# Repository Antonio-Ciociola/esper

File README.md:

# Esper

An esp32 based eurorack module.

## Specifications

- 8HP width
- 4 CV inputs
- 2 Audio Outputs
- Oled Display with LVGL GUI
- Rotary Encoder with Push Button
- Esp32s3 has 2 cores, Bluetooth and Wifi support

## Photos

## Future Plans and Issues

- Better alternative to external adc for cv inputs
- Codec chip for both audio in and out, to allow for audio processing
- The esp32s3 floating point performance is not great

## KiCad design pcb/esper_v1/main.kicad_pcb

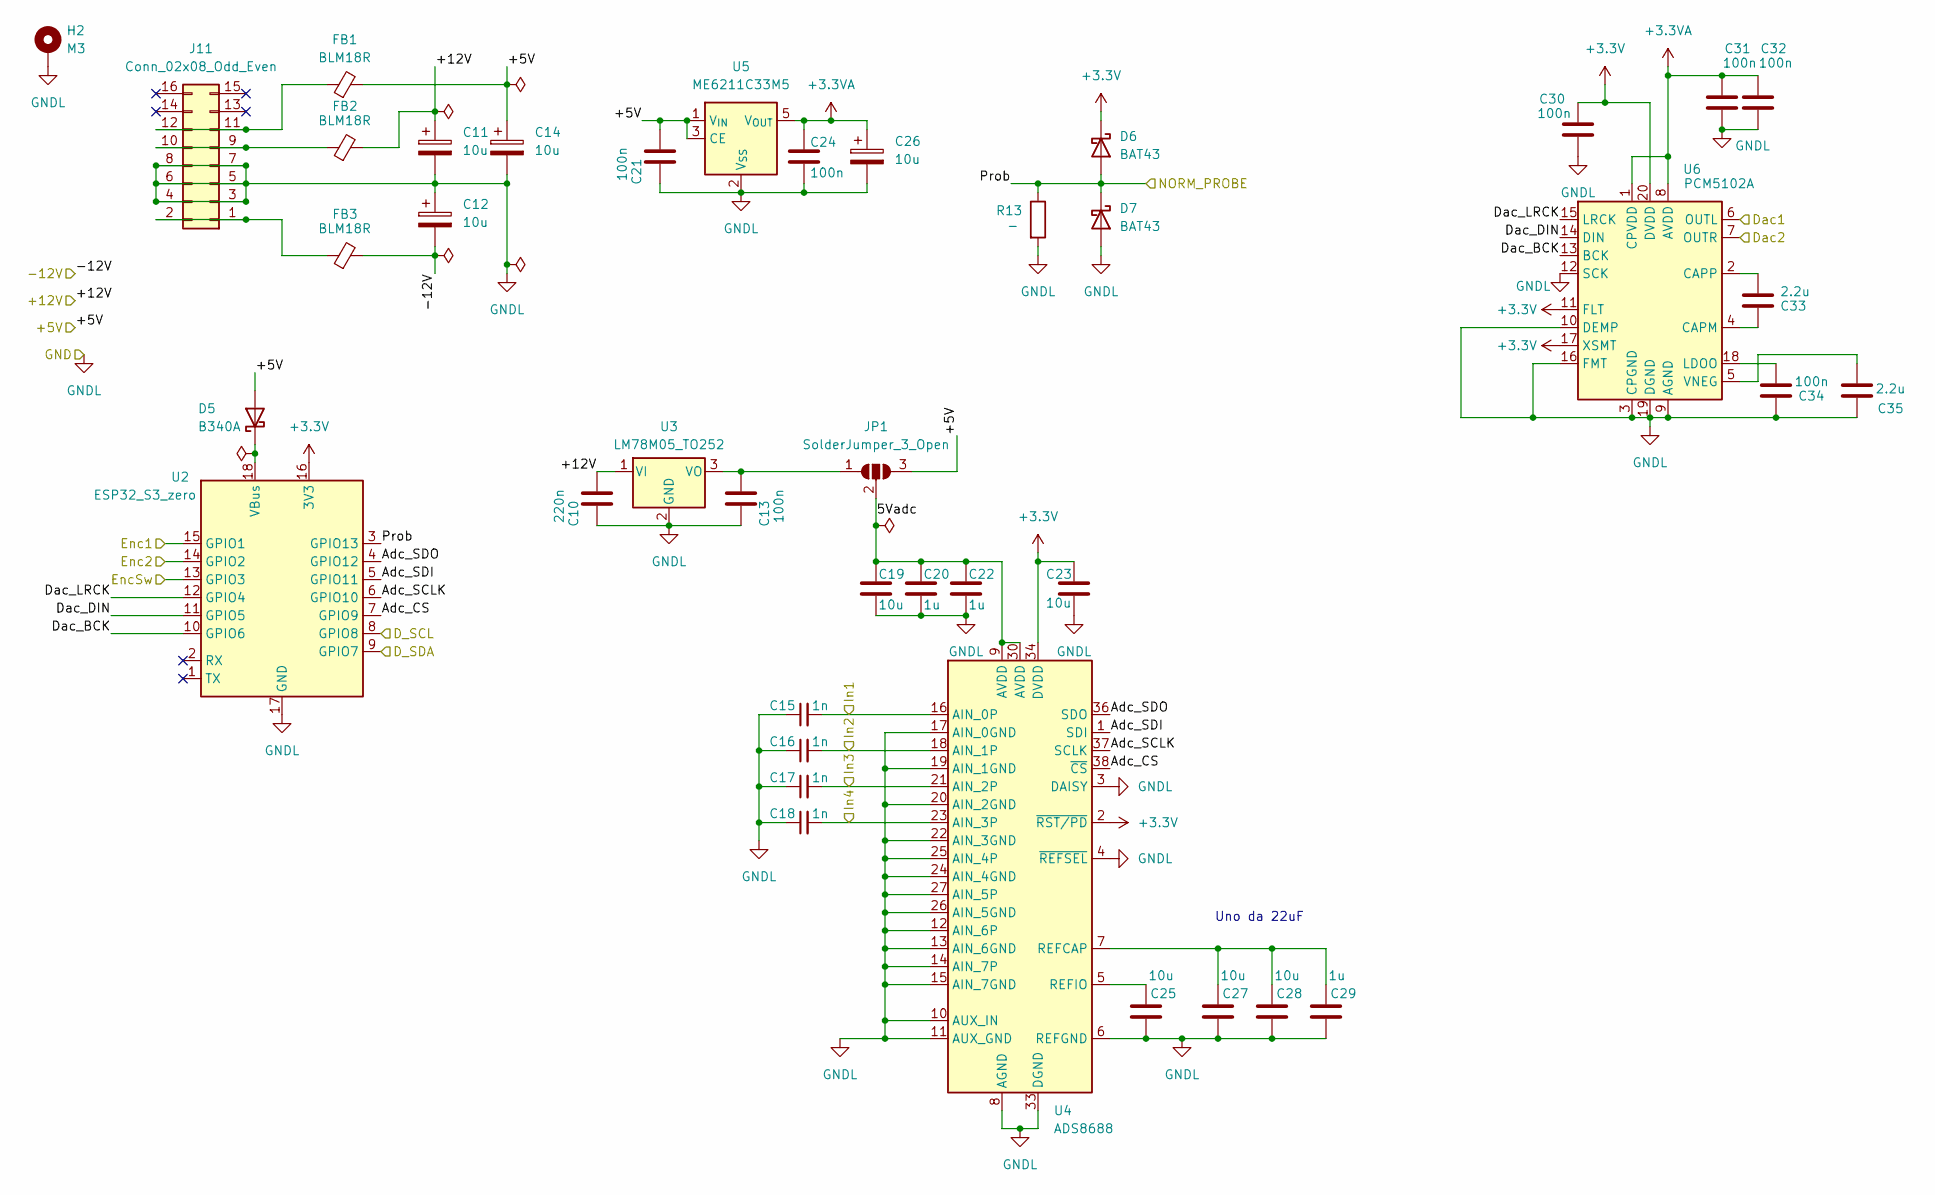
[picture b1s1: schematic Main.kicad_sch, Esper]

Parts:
C10: 220n; C_0603_1608Metric
C11, C12, C14, C26: 10u; CP_Radial_D5.0mm_P2.50mm
C13, C21, C24, C30, C31, C32, C34: 100n; C_0603_1608Metric
C15, C16, C17, C18: 1n; C_0603_1608Metric
C19, C23, C25, C27, C28: 10u; C_0603_1608Metric
C20, C22, C29: 1u; C_0603_1608Metric
C33, C35: 2.2u; C_0603_1608Metric
D5: B340A; D_SMA
D6, D7: BAT43; D_SOD-123
FB1, FB2, FB3: BLM18R; L_0603_1608Metric
H2: M3; MountingHole_3.2mm_M3_Pad
J11: Conn_02x08_Odd_Even; IDC-Header_2x08_P2.54mm_Vertical
JP1: SolderJumper_3_Open; SolderJumper-3_P1.3mm_Open_RoundedPad1.0x1.5mm_NumberLabels
R13: _; R_0603_1608Metric
U2: ESP32_S3_zero; Esp32-S3 Zero
U3: LM78M05_TO252; TO-252-3_TabPin2
U4: ADS8688; TSSOP-38_4.4x9.7mm_P0.5mm
U5: ME6211C33M5; SOT-23-5
U6: PCM5102A; TSSOP-20_4.4x6.5mm_P0.65mm

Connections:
+3.3V: C23.1, C30.1, D6.1 (K), U2.16 (3V3), U4.2 (~RST/PD), U4.34 (DVDD), U6.11 (FLT), U6.17 (XSMT), U6.20 (DVDD)
+3.3VA: C24.2, C26.1, C31.1, C32.1, U5.5 (V_{OUT}), U6.1 (CPVDD), U6.8 (AVDD)
+5V: C14.1, C21.1, D5.2 (A), FB1.2, JP1.3 (B), U5.1 (V_{IN}), U5.3 (CE); also elsewhere on the board
+12V: C10.1, C11.1, FB2.2, U3.1 (VI); also elsewhere on the board
-12V: C12.2, FB3.2; also elsewhere on the board
/Main/5Vadc: C19.1, C20.1, C22.1, JP1.2 (C), U4.9 (AVDD), U4.30 (AVDD)
/Main/Adc_CS: U2.7 (GPIO9), U4.38 (~CS)
/Main/Adc_SCLK: U2.6 (GPIO10), U4.37 (SCLK)
/Main/Adc_SDI: U2.5 (GPIO11), U4.1 (SDI)
/Main/Adc_SDO: U2.4 (GPIO12), U4.36 (SDO)
/Main/D_SCL: U2.8 (GPIO8); also elsewhere on the board
/Main/D_SDA: U2.9 (GPIO7); also elsewhere on the board
/Main/Dac1: U6.6 (OUTL); also elsewhere on the board
/Main/Dac2: U6.7 (OUTR); also elsewhere on the board
/Main/Dac_BCK: U2.10 (GPIO6), U6.13 (BCK)
/Main/Dac_DIN: U2.11 (GPIO5), U6.14 (DIN)
/Main/Dac_LRCK: U2.12 (GPIO4), U6.15 (LRCK)
/Main/Enc1: U2.15 (GPIO1); also elsewhere on the board
/Main/Enc2: U2.14 (GPIO2); also elsewhere on the board
/Main/EncSw: U2.13 (GPIO3); also elsewhere on the board
/Main/In1: C15.2, U4.16 (AIN_0P); also elsewhere on the board
/Main/In2: C16.2, U4.18 (AIN_1P); also elsewhere on the board
/Main/In3: C17.2, U4.21 (AIN_2P); also elsewhere on the board
/Main/In4: C18.2, U4.23 (AIN_3P); also elsewhere on the board
/Main/Prob: D6.2 (A), D7.1 (K), R13.1, U2.3 (GPIO13); also elsewhere on the board
GND: C10.2, C11.2, C12.1, C13.2, C14.2, C15.1, C16.1, C17.1, C18.1, C19.2, C20.2, C21.2, C22.2, C23.2, C24.1, C25.2, C26.2, C27.2, C28.2, C29.2, C30.2, C31.2, C32.2, C34.2, C35.2, D7.2 (A), H2.1, J11.3, J11.4, J11.5, J11.6, J11.7, J11.8, R13.2, U2.17 (GND), U3.2 (GND), U4.3 (DAISY), U4.4 (~REFSEL), U4.6 (REFGND), U4.8 (AGND), U4.10 (AUX_IN), U4.11 (AUX_GND), U4.12 (AIN_6P), U4.13 (AIN_6GND), U4.14 (AIN_7P), U4.15 (AIN_7GND), U4.17 (AIN_0GND), U4.19 (AIN_1GND), U4.20 (AIN_2GND), U4.22 (AIN_3GND), U4.24 (AIN_4GND), U4.25 (AIN_4P), U4.26 (AIN_5GND), U4.27 (AIN_5P), U4.28 (AGND), U4.29 (AGND), U4.31 (AGND), U4.32 (AGND), U4.33 (DGND), U5.2 (V_{SS}), U6.3 (CPGND), U6.9 (AGND), U6.10 (DEMP), U6.12 (SCK), U6.16 (FMT), U6.19 (DGND); also elsewhere on the board
unnamed: D5.1 (K), U2.18 (VBus)
unnamed: FB3.1, J11.1, J11.2
unnamed: FB2.1, J11.9, J11.10
unnamed: FB1.1, J11.11, J11.12
unnamed: C13.1, JP1.1 (A), U3.3 (VO)
unnamed: C27.1, C28.1, C29.1, U4.7 (REFCAP)
unnamed: C25.1, U4.5 (REFIO)
unnamed: C33.2, U6.4 (CAPM)
unnamed: C33.1, U6.2 (CAPP)
unnamed: C34.1, U6.18 (LDOO)
unnamed: C35.1, U6.5 (VNEG)

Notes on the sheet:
Uno da 22uF

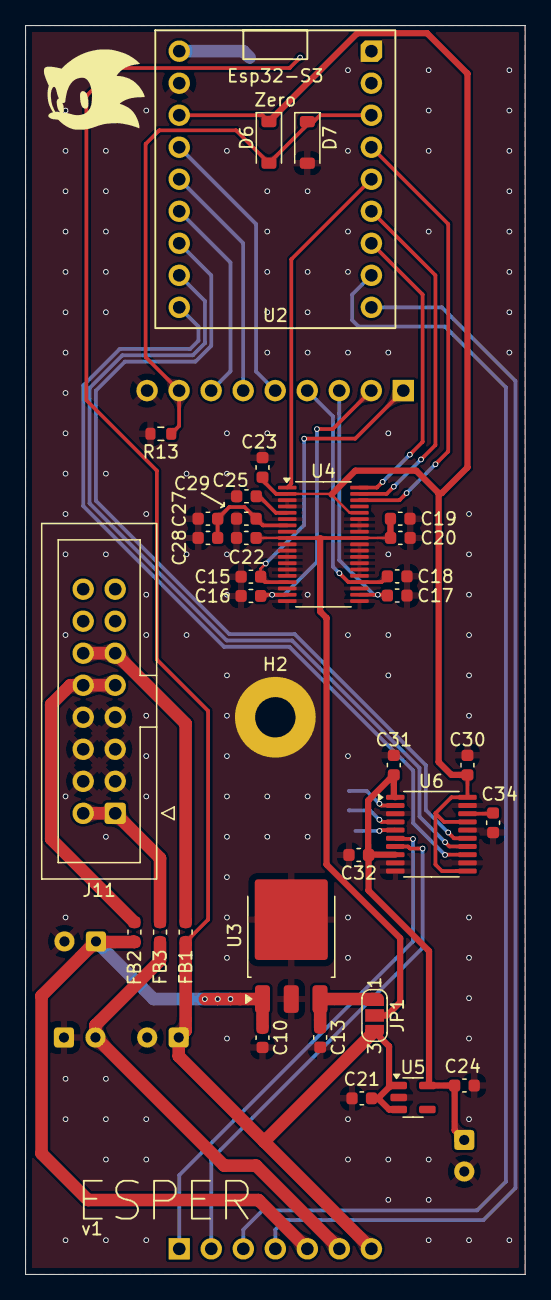
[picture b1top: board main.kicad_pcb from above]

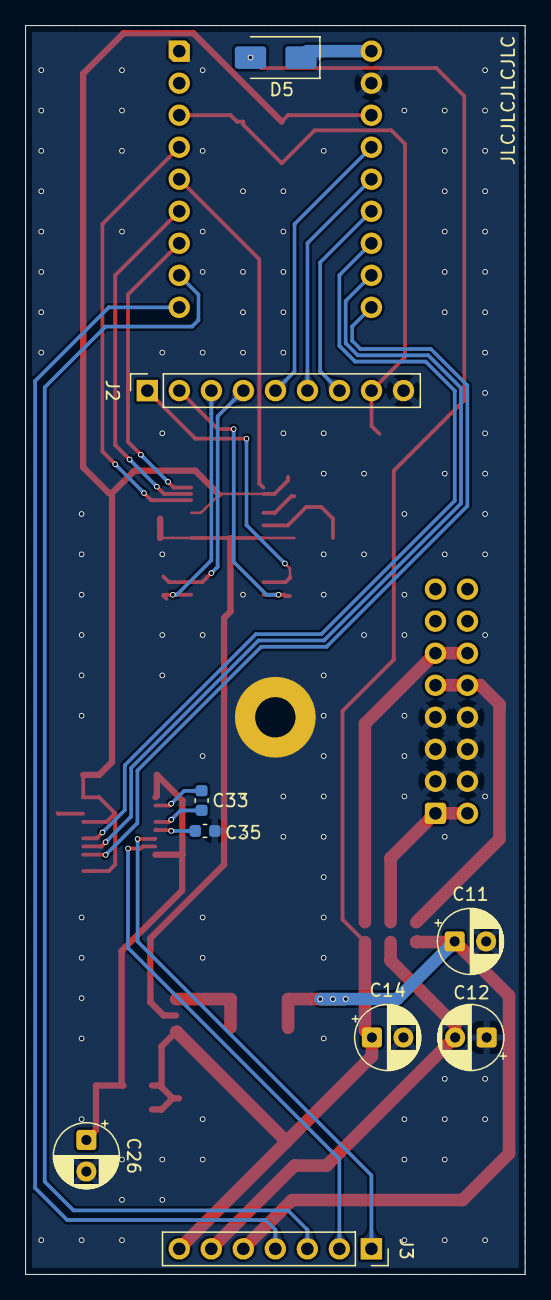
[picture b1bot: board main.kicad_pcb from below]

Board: 2 copper layers, 39.6 x 99.1 mm, 43 parts (9 on the bottom side), 37 nets.

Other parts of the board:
J2: m_in_Con; PinSocket_1x09_P2.54mm_Vertical
J3: m_Out_Con; PinSocket_1x07_P2.54mm_Vertical

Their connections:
+5V: J3.7; also elsewhere on the board
+12V: J3.5; also elsewhere on the board
-12V: J3.6; also elsewhere on the board
/Main/D_SCL: J3.3; also elsewhere on the board
/Main/D_SDA: J3.4; also elsewhere on the board
/Main/Dac1: J3.1; also elsewhere on the board
/Main/Dac2: J3.2; also elsewhere on the board
/Main/Enc1: J2.5; also elsewhere on the board
/Main/Enc2: J2.6; also elsewhere on the board
/Main/EncSw: J2.7; also elsewhere on the board
/Main/In1: J2.1; also elsewhere on the board
/Main/In2: J2.2; also elsewhere on the board
/Main/In3: J2.3; also elsewhere on the board
/Main/In4: J2.4; also elsewhere on the board
/Main/Prob: J2.8; also elsewhere on the board
GND: J2.9; also elsewhere on the board

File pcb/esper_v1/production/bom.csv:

Designator,Footprint,Quantity,Value,LCSC Part #
C10,0603,1,220n,
"C11, C12, C14, C26",CP_Radial_D5.0mm_P2.50mm,4,10u,
"C13, C21, C24, C30, C31, C32, C34",0603,7,100n,
"C15, C16, C17, C18",0603,4,1n,
"C19, C23, C25, C27, C28",0603,5,10u,
"C20, C22, C29",0603,3,1u,
"C33, C35",0603,2,2.2u,
D5,D_SMA,1,B340A,
"D6, D7",D_SOD-123,2,BAT43,
"FB1, FB2, FB3",0603,3,BLM18R,
J11,IDC-Header_2x08_P2.54mm_Vertical,1,Conn_02x08_Odd_Even,
J2,PinSocket_1x09_P2.54mm_Vertical,1,m_in_Con,
J3,PinSocket_1x07_P2.54mm_Vertical,1,m_Out_Con,
R13,0603,1,_,
U2,Esp32-S3 Zero,1,ESP32_S3_zero,
U3,TO-252-3_TabPin2,1,LM78M05_TO252,
U4,TSSOP-38_4.4x9.7mm_P0.5mm,1,ADS8688,
U5,SOT-23-5,1,ME6211C33M5,
U6,TSSOP-20_4.4x6.5mm_P0.65mm,1,PCM5102A,

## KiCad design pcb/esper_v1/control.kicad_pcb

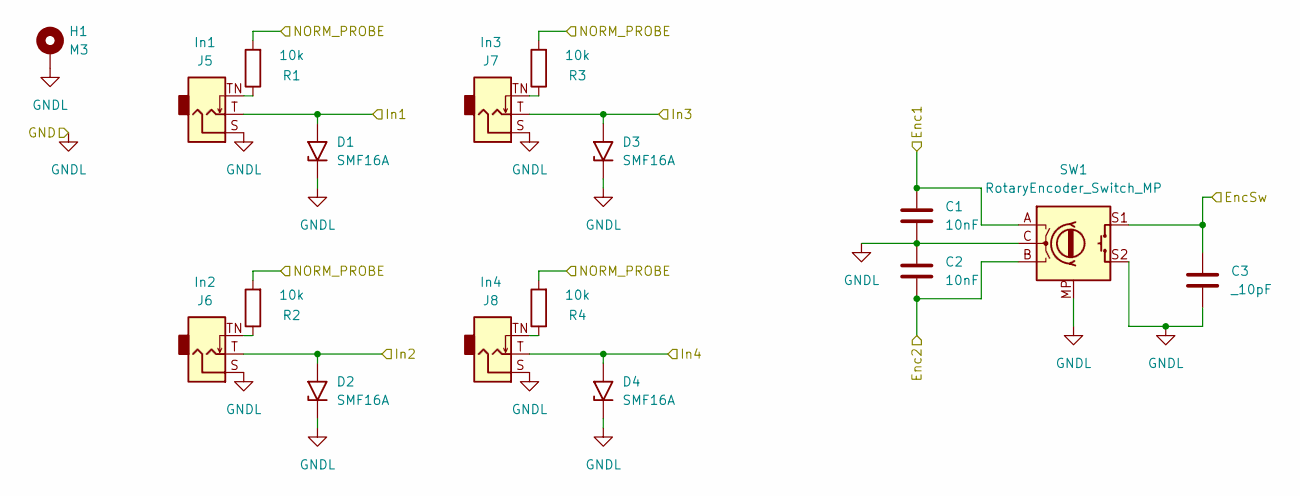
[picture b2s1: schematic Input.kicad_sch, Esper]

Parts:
C1, C2: 10nF; C_0603_1608Metric
C3: _10pF; C_0603_1608Metric
D1, D2, D3, D4: SMF16A; D_SMF
H1: M3; MountingHole_3.2mm_M3_Pad
J5: In1; Jack
J6: In2; Jack
J7: In3; Jack
J8: In4; Jack
R1, R2, R3, R4: 10k; R_0603_1608Metric
SW1: RotaryEncoder_Switch_MP; RotaryEncoder_Switch

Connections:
/Input/Enc1: C1.1, SW1.A; also elsewhere on the board
/Input/Enc2: C2.2, SW1.B; also elsewhere on the board
/Input/EncSw: C3.1, SW1.S1; also elsewhere on the board
/Input/In1: D1.2 (A2), J5.T; also elsewhere on the board
/Input/In2: D2.2 (A2), J6.T; also elsewhere on the board
/Input/In3: D3.2 (A2), J7.T; also elsewhere on the board
/Input/In4: D4.2 (A2), J8.T; also elsewhere on the board
/Input/NORM_PROBE: R1.2, R2.2, R3.2, R4.2; also elsewhere on the board
GNDL: C1.2, C2.1, C3.2, D1.1 (A1), D2.1 (A1), D3.1 (A1), D4.1 (A1), H1.1, J5.S, J6.S, J7.S, J8.S, SW1.C, SW1.MP, SW1.S2; also elsewhere on the board
unnamed: J5.TN, R1.1
unnamed: J6.TN, R2.1
unnamed: J7.TN, R3.1
unnamed: J8.TN, R4.1

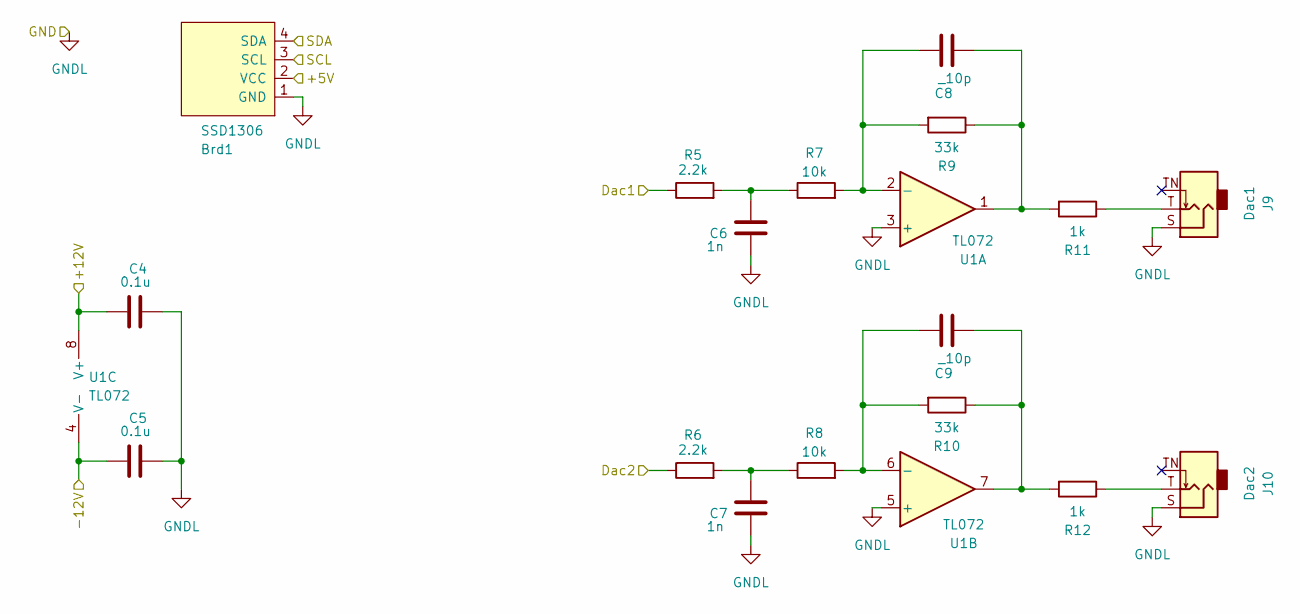
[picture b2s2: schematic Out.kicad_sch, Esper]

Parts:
Brd1: SSD1306; 128x64OLED
C4, C5: 0.1u; C_0603_1608Metric
C6, C7: 1n; C_0603_1608Metric
C8, C9: _10p; C_0603_1608Metric
J9: Dac1; Jack
J10: Dac2; Jack
R5, R6: 2.2k; R_0603_1608Metric
R7, R8: 10k; R_0603_1608Metric
R9, R10: 33k; R_0603_1608Metric
R11, R12: 1k; R_0603_1608Metric
U1: TL072; SOIC-8_3.9x4.9mm_P1.27mm

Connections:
/Out/+5V: Brd1.2 (VCC); also elsewhere on the board
/Out/+12V: C4.1, U1.8 (V+); also elsewhere on the board
/Out/-12V: C5.1, U1.4 (V-); also elsewhere on the board
/Out/Dac1: R5.1; also elsewhere on the board
/Out/Dac2: R6.1; also elsewhere on the board
/Out/SCL: Brd1.3 (SCL); also elsewhere on the board
/Out/SDA: Brd1.4 (SDA); also elsewhere on the board
GNDL: Brd1.1 (GND), C4.2, C5.2, C6.1, C7.1, J9.S, J10.S, U1.3 (+), U1.5 (+); also elsewhere on the board
unnamed: C6.2, R5.2, R7.1
unnamed: C7.2, R6.2, R8.1
unnamed: C8.1, R9.1, R11.2, U1.1
unnamed: C9.1, R10.1, R12.2, U1.7
unnamed: J9.T, R11.1
unnamed: J10.T, R12.1
unnamed: C8.2, R7.2, R9.2, U1.2 (-)
unnamed: C9.2, R8.2, R10.2, U1.6 (-)

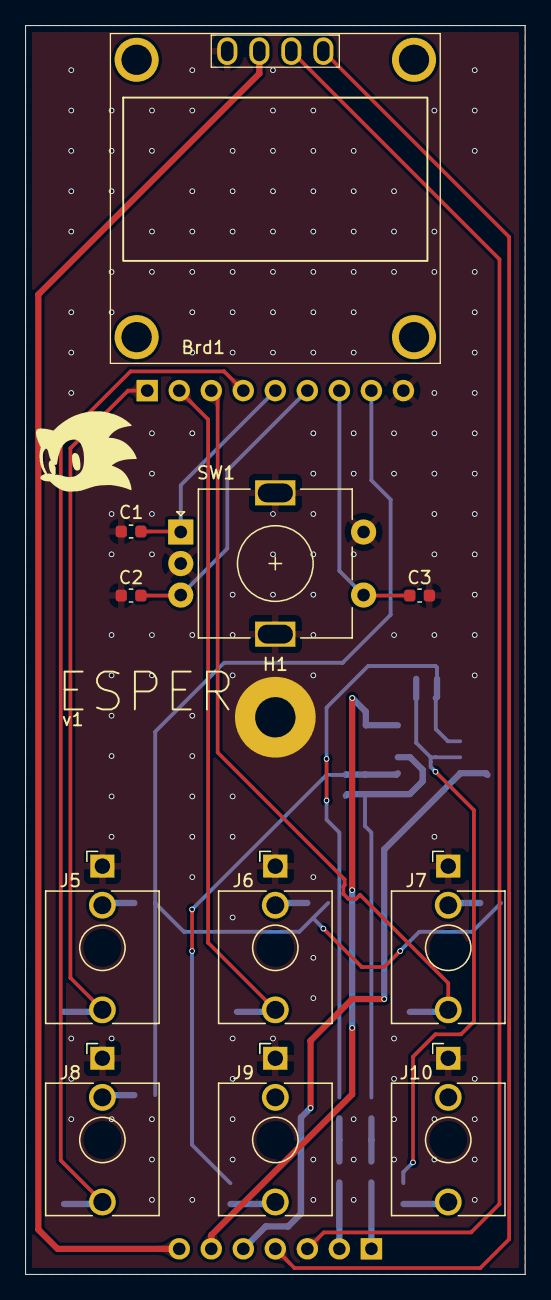
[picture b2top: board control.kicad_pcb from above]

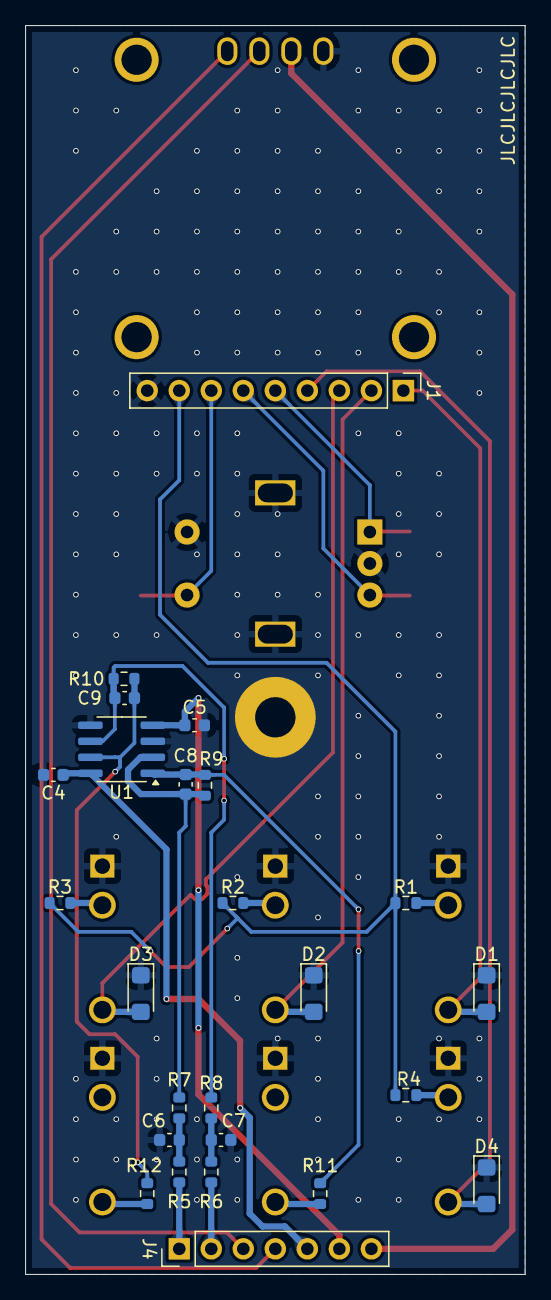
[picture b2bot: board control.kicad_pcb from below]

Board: 2 copper layers, 39.6 x 99.1 mm, 37 parts (25 on the bottom side), 28 nets.

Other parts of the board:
J1: c_In_Con; PinHeader_1x09_P2.54mm_Vertical
J4: c_Out_Con; PinHeader_1x07_P2.54mm_Vertical

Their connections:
/Input/Enc1: J1.5; also elsewhere on the board
/Input/Enc2: J1.6; also elsewhere on the board
/Input/EncSw: J1.7; also elsewhere on the board
/Input/In1: J1.1; also elsewhere on the board
/Input/In2: J1.2; also elsewhere on the board
/Input/In3: J1.3; also elsewhere on the board
/Input/In4: J1.4; also elsewhere on the board
/Input/NORM_PROBE: J1.8; also elsewhere on the board
/Out/+5V: J4.7; also elsewhere on the board
/Out/+12V: J4.5; also elsewhere on the board
/Out/-12V: J4.6; also elsewhere on the board
/Out/Dac1: J4.1; also elsewhere on the board
/Out/Dac2: J4.2; also elsewhere on the board
/Out/SCL: J4.3; also elsewhere on the board
/Out/SDA: J4.4; also elsewhere on the board
GNDL: J1.9; also elsewhere on the board
